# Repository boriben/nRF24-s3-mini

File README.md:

## ESP32-S3-mini + Ebyte nRF24 multi-purpose controller PCB 
### Features/components:
- ESP32-S3-mini-1U connected via SPI to Ebyte E01 2G4M27SX (nRF24) 
- Power from USB-C or lithium battery
- BQ2409 lithium battery charger IC with switch to toggle between 1A and 257mA fast-charge rate
- Resistor divider to monitor battery level
- Buck-boost converter to maintain 3.3V output across battery life
- Joystick, buttons, extra GPIOs for UART, I2C OLED, power, etc.
- flash ESP32 via USB-C

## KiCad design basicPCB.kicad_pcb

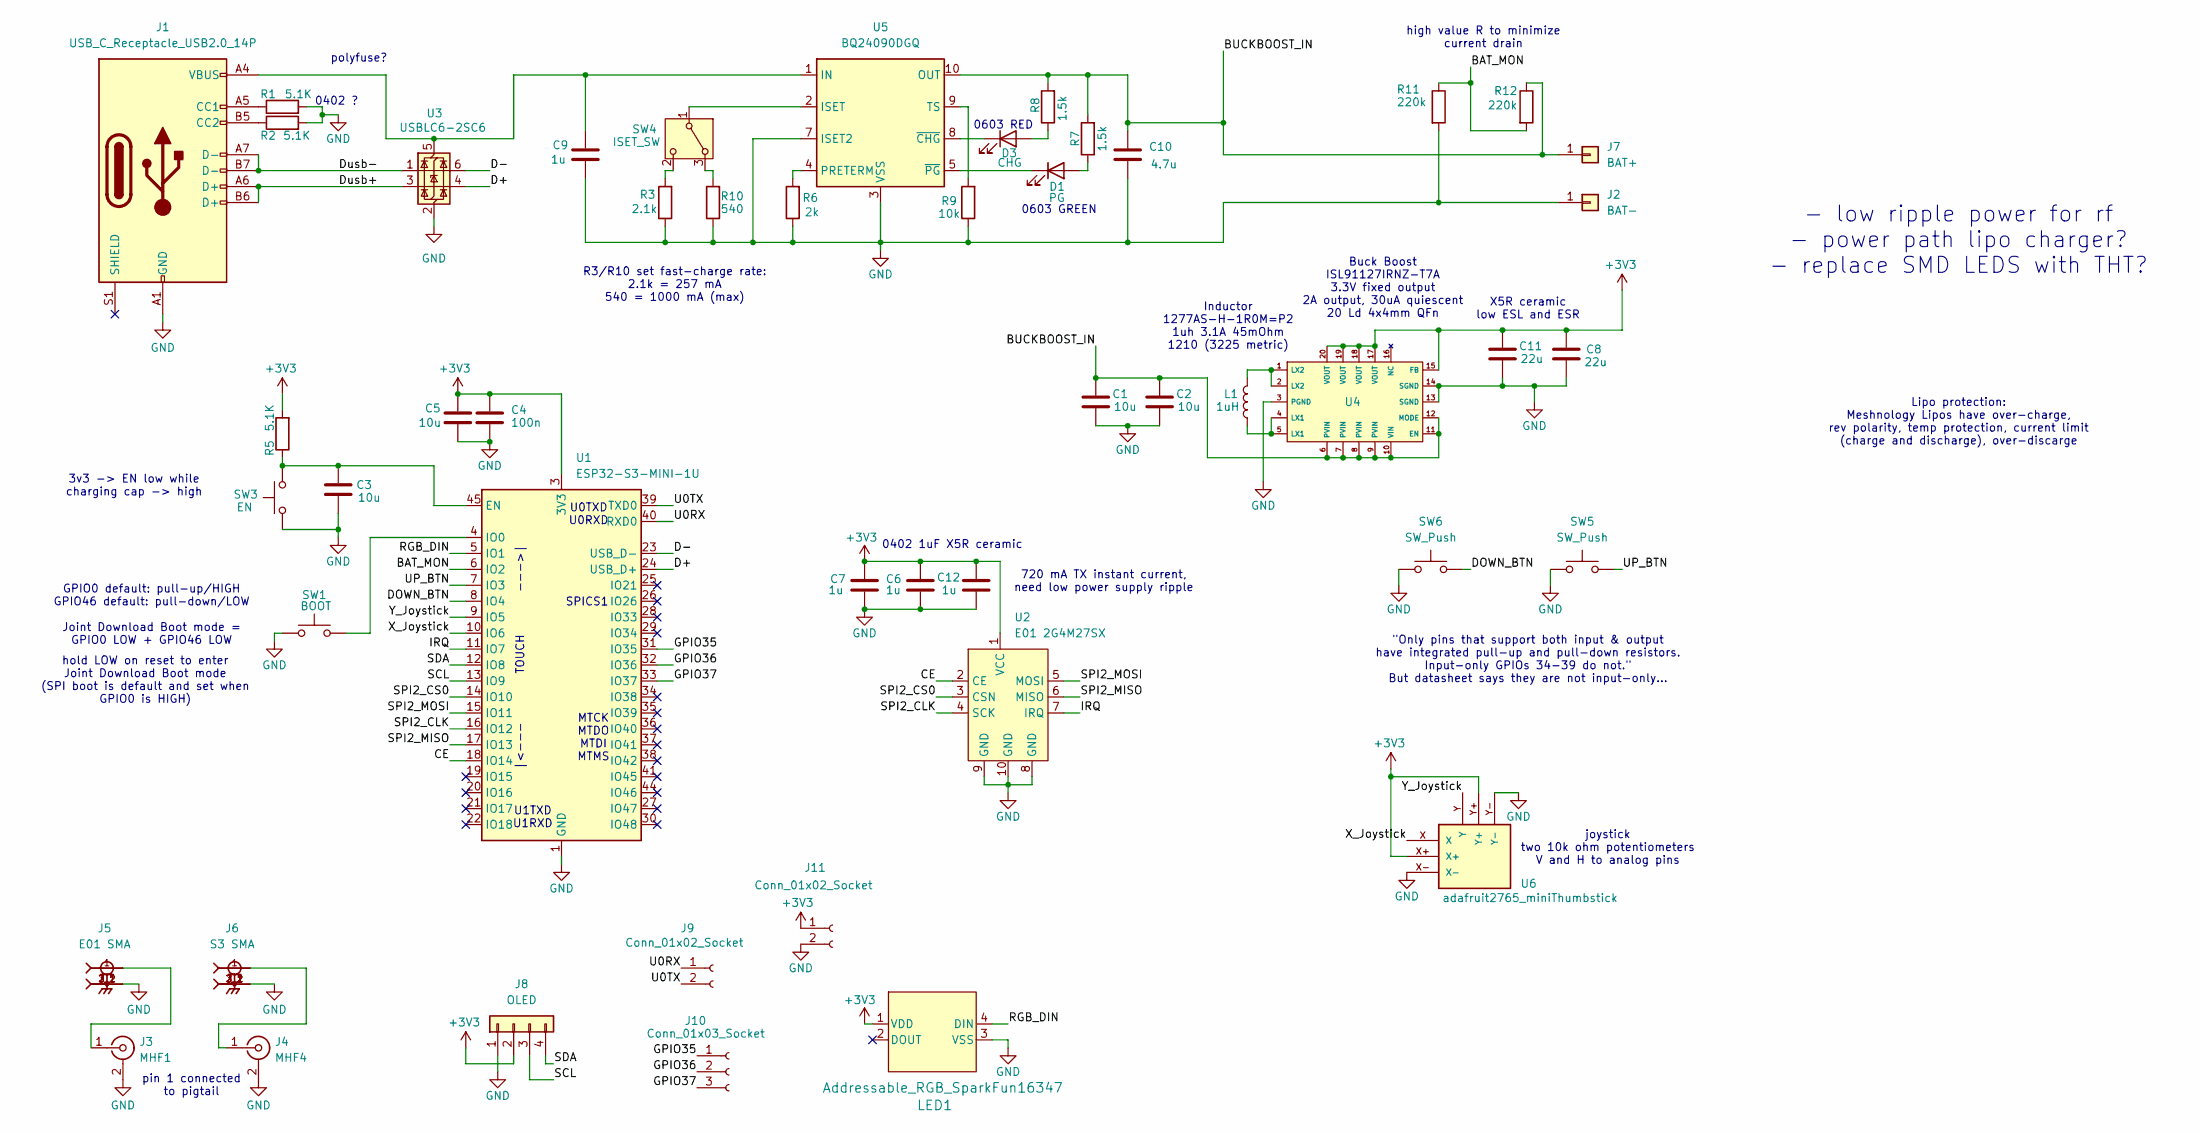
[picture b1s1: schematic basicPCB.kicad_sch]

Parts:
C1, C2: 10u; C_0603_1608Metric
C3, C5: 10u; C_0402_1005Metric
C4: 100n; C_0402_1005Metric
C6, C7, C9, C12: 1u; C_0402_1005Metric
C8, C11: 22u; C_0603_1608Metric
C10: 4.7u; C_0402_1005Metric
D1: PG; LED_0603_1608Metric
D3: CHG; LED_0603_1608Metric
J1: USB_C_Receptacle_USB2.0_14P; USB_C_Receptacle_G-Switch_GT-USB-7010ASV
J2: BAT-; PinHeader_1x01_P2.54mm_Vertical
J3: MHF1; U.FL_Molex_MCRF_73412-0110_Vertical
J4: MHF4; IPEX_20449-001E-03
J5: E01 SMA; SAMTEC_SMA-J-P-H-ST-EM1; PARTREV G
J6: S3 SMA; SAMTEC_SMA-J-P-H-ST-EM1; PARTREV G
J7: BAT+; PinHeader_1x01_P2.54mm_Vertical
J8: OLED; PinHeader_1x04_P2.54mm_Vertical
J9, J11: Conn_01x02_Socket; PinHeader_1x02_P2.54mm_Vertical
J10: Conn_01x03_Socket; PinHeader_1x03_P2.54mm_Vertical
L1: 1uH; 1277AS-H-1R0M=P2
LED1: Addressable_RGB_SparkFun16347; SparkFun_16347_AddressableRGB
R1, R2, R5: 5.1K; R_0402_1005Metric
R3: 2.1k; R_0402_1005Metric
R6: 2k; R_0402_1005Metric
R7, R8: 1.5k; R_0402_1005Metric
R9: 10k; R_0402_1005Metric
R10: 540; R_0402_1005Metric
R11, R12: 220k; R_0402_1005Metric
SW1: BOOT; 3x4x2mm button
SW3: EN; 3x4x2mm button
SW4: ISET_SW; SW_Slide-03_Wuerth-WS-SLTV_10x2.5x6.4_P2.54mm
SW5, SW6: SW_Push; SW_PUSH-12mm
U1: ESP32-S3-MINI-1U; ESP32-S2-MINI-1U
U2: E01 2G4M27SX; Ebyte E01 2G4M27SX
U3: USBLC6-2SC6; SOT-23-6
U4: QFN-20-1EP_4x4mm_P0.5mm_EP2.5x2.5mm
U5: BQ24090DGQ; HVSSOP-10-1EP_3x3mm_P0.5mm_EP1.57x1.88mm_ThermalVias
U6: adafruit2765_miniThumbstick; PARTREV N/A

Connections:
+3V3: C4.1, C5.1, C6.1, C7.1, C8.1, C11.1, C12.1, J8.2, J11.1, LED1.1 (VDD), R5.2, U1.3 (3V3), U2.1 (VCC), U4.15 (FB), U4.17 (VOUT), U4.18 (VOUT), U4.19 (VOUT), U4.20 (VOUT), U6.X+, U6.Y+
/BAT_MON: R11.1, R12.2, U1.6 (IO2)
/BUCKBOOST_IN: C1.1, C2.1, C10.1, J7.1, R7.2, R8.2, R12.1, U4.6 (PVIN), U4.7 (PVIN), U4.8 (PVIN), U4.9 (PVIN), U4.10 (VIN), U4.11 (EN), U4.12 (MODE), U5.10 (OUT)
/CE: U1.18 (IO14), U2.2 (CE)
/D+: U1.24 (USB_D+), U3.4 (I/O2)
/D-: U1.23 (USB_D-), U3.6 (I/O1)
/DOWN_BTN: SW6.2, U1.8 (IO4)
/Dusb+: J1.A6 (D+), J1.B6 (D+), U3.3 (I/O2)
/Dusb-: J1.A7 (D-), J1.B7 (D-), U3.1 (I/O1)
/GPIO35: J10.1, U1.31 (IO35)
/GPIO36: J10.2, U1.32 (IO36)
/GPIO37: J10.3, U1.33 (IO37)
/IRQ: U1.11 (IO7), U2.7 (IRQ)
/RGB_DIN: LED1.4 (DIN), U1.5 (IO1)
/SCL: J8.3, U1.13 (IO9)
/SDA: J8.4, U1.12 (IO8)
/SPI2_CLK: U1.16 (IO12), U2.4 (SCK)
/SPI2_CS0: U1.14 (IO10), U2.3 (CSN)
/SPI2_MISO: U1.17 (IO13), U2.6 (MISO)
/SPI2_MOSI: U1.15 (IO11), U2.5 (MOSI)
/U0RX: J9.1, U1.40 (RXD0)
/U0TX: J9.2, U1.39 (TXD0)
/UP_BTN: SW5.2, U1.7 (IO3)
/X_Joystick: U1.10 (IO6), U6.X
/Y_Joystick: U1.9 (IO5), U6.Y
GND: C1.2, C2.2, C3.2, C4.2, C5.2, C6.2, C7.2, C8.2, C9.2, C10.2, C11.2, C12.2, J1.A1 (GND), J1.A12 (GND), J1.B1 (GND), J1.B12 (GND), J2.1, J3.2 (Ext), J4.2 (Ext), J5.2_1, J5.2_2, J5.3_1, J5.3_2, J6.2_1, J6.2_2, J6.3_1, J6.3_2, J8.1, J11.2, LED1.3 (VSS), R1.2, R2.2, R3.1, R6.1, R9.1, R10.1, R11.2, SW1.1, SW3.1, SW5.1, SW6.1, U1.1 (GND), U1.2 (GND), U1.42 (GND), U1.43 (GND), U1.46 (GND), U1.47 (GND), U1.48 (GND), U1.49 (GND), U1.50 (GND), U1.51 (GND), U1.52 (GND), U1.53 (GND), U1.54 (GND), U1.55 (GND), U1.56 (GND), U1.57 (GND), U1.58 (GND), U1.59 (GND), U1.60 (GND), U1.61 (GND), U1.62 (GND), U1.63 (GND), U1.64 (GND), U1.65 (GND), U2.8 (GND), U2.9 (GND), U2.10 (GND), U3.2 (GND), U4.3 (PGND), U4.13 (SGND), U4.14 (SGND), U5.3 (VSS), U5.7 (ISET2), U5.11 (VSS), U6.X-, U6.Y-
unnamed: D1.2 (A), R7.1
unnamed: D1.1 (K), U5.5 (~PG)
unnamed: D3.2 (A), R8.1
unnamed: D3.1 (K), U5.8 (~CHG)
unnamed: J1.A5 (CC1), R1.1
unnamed: J1.B5 (CC2), R2.1
unnamed: J3.1 (In), J5.1
unnamed: J4.1 (In), J6.1
unnamed: L1.1, U4.4 (LX1), U4.5 (LX1)
unnamed: L1.2, U4.1 (LX2), U4.2 (LX2)
unnamed: R10.2, SW4.3 (A)
unnamed: SW4.1 (B), U5.2 (ISET)
unnamed: R3.2, SW4.2 (C)
unnamed: C3.1, R5.1, SW3.2, U1.45 (EN)
unnamed: SW1.2, U1.4 (IO0)
unnamed: C9.1, J1.A4 (VBUS), J1.A9 (VBUS), J1.B4 (VBUS), J1.B9 (VBUS), U3.5 (VBUS), U5.1 (IN)
unnamed: R6.2, U5.4 (PRETERM)
unnamed: R9.2, U5.9 (TS)

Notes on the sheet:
Buck Boost ISL91127IRNZ-T7A 3.3V fixed output 2A output, 30uA quiescent 20 Ld 4x4mm QFn
polyfuse?
|<--- TOUCH --->|
3v3 -> EN low while charging cap -> high
high value R to minimize current drain
X5R ceramic low ESL and ESR
U0TXD U0RXD
joystick two 10k ohm potentiometers V and H to analog pins
U1TXD U1RXD
"Only pins that support both input & output have integrated pull-up and pull-down resistors. Input-only GPIOs 34-39 do not." But datasheet says they are not input-only...
720 mA TX instant current, need low power supply ripple
SPICS1
Lipo protection: Meshnology Lipos have over-charge, rev polarity, temp protection, current limit (charge and discharge), over-discarge
- low ripple power for rf - power path lipo charger? - replace SMD LEDS with THT?
hold LOW on reset to enter Joint Download Boot mode (SPI boot is default and set when GPIO0 is HIGH)
R3/R10 set fast-charge rate: 2.1k = 257 mA 540 = 1000 mA (max)
0402 ?
0402 1uF X5R ceramic
Inductor 1277AS-H-1R0M=P2 1uh 3.1A 45mOhm 1210 (3225 metric)
0603 GREEN
pin 1 connected to pigtail
GPIO0 default: pull-up/HIGH GPIO46 default: pull-down/LOW Joint Download Boot mode = GPIO0 LOW + GPIO46 LOW
0603 RED
MTCK MTDO MTDI MTMS

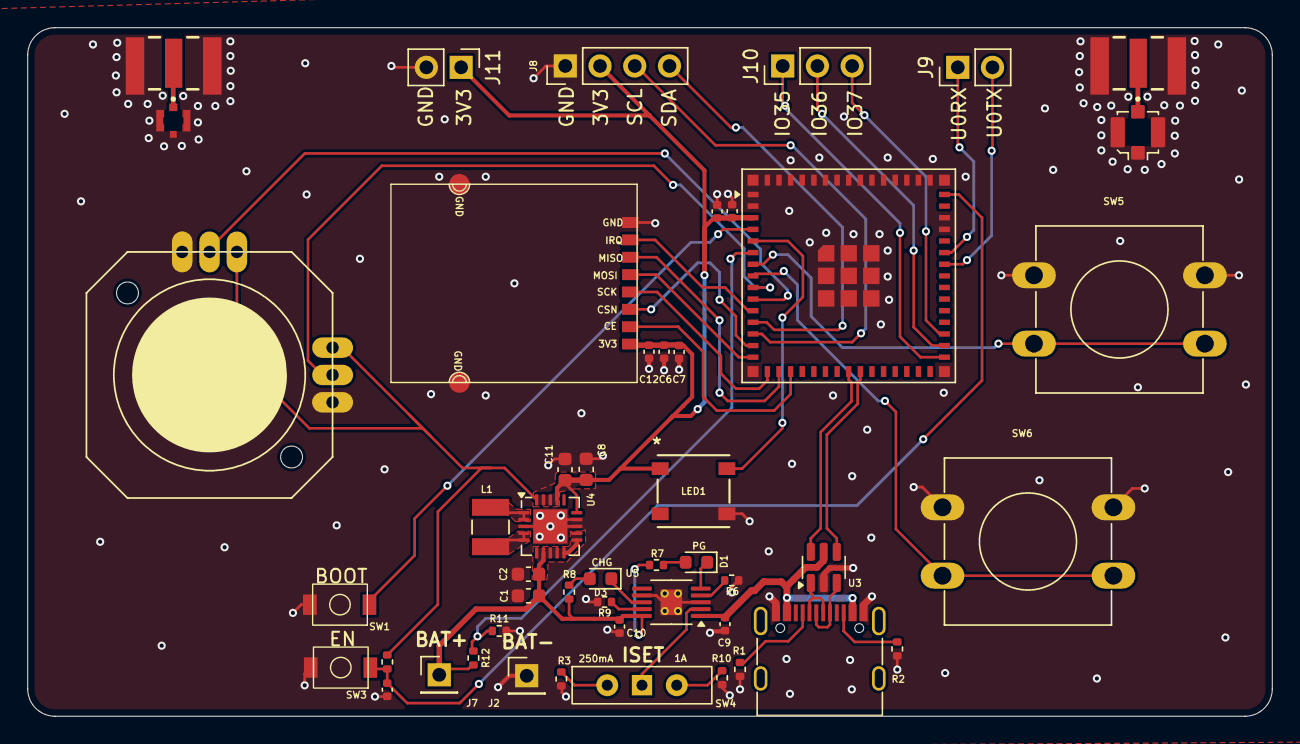
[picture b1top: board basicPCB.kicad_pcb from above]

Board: 4 copper layers, 91.0 x 50.4 mm, 49 parts (0 on the bottom side), 44 nets.

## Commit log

2026-01-13 init commit
2026-01-14 removed more files from git
